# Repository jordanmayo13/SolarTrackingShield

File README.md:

# SolarTrackingSheild
ENGI 5800 Junior Design Project. An open source Arduino UNO R3 shield with room for a solar panel powered payload.

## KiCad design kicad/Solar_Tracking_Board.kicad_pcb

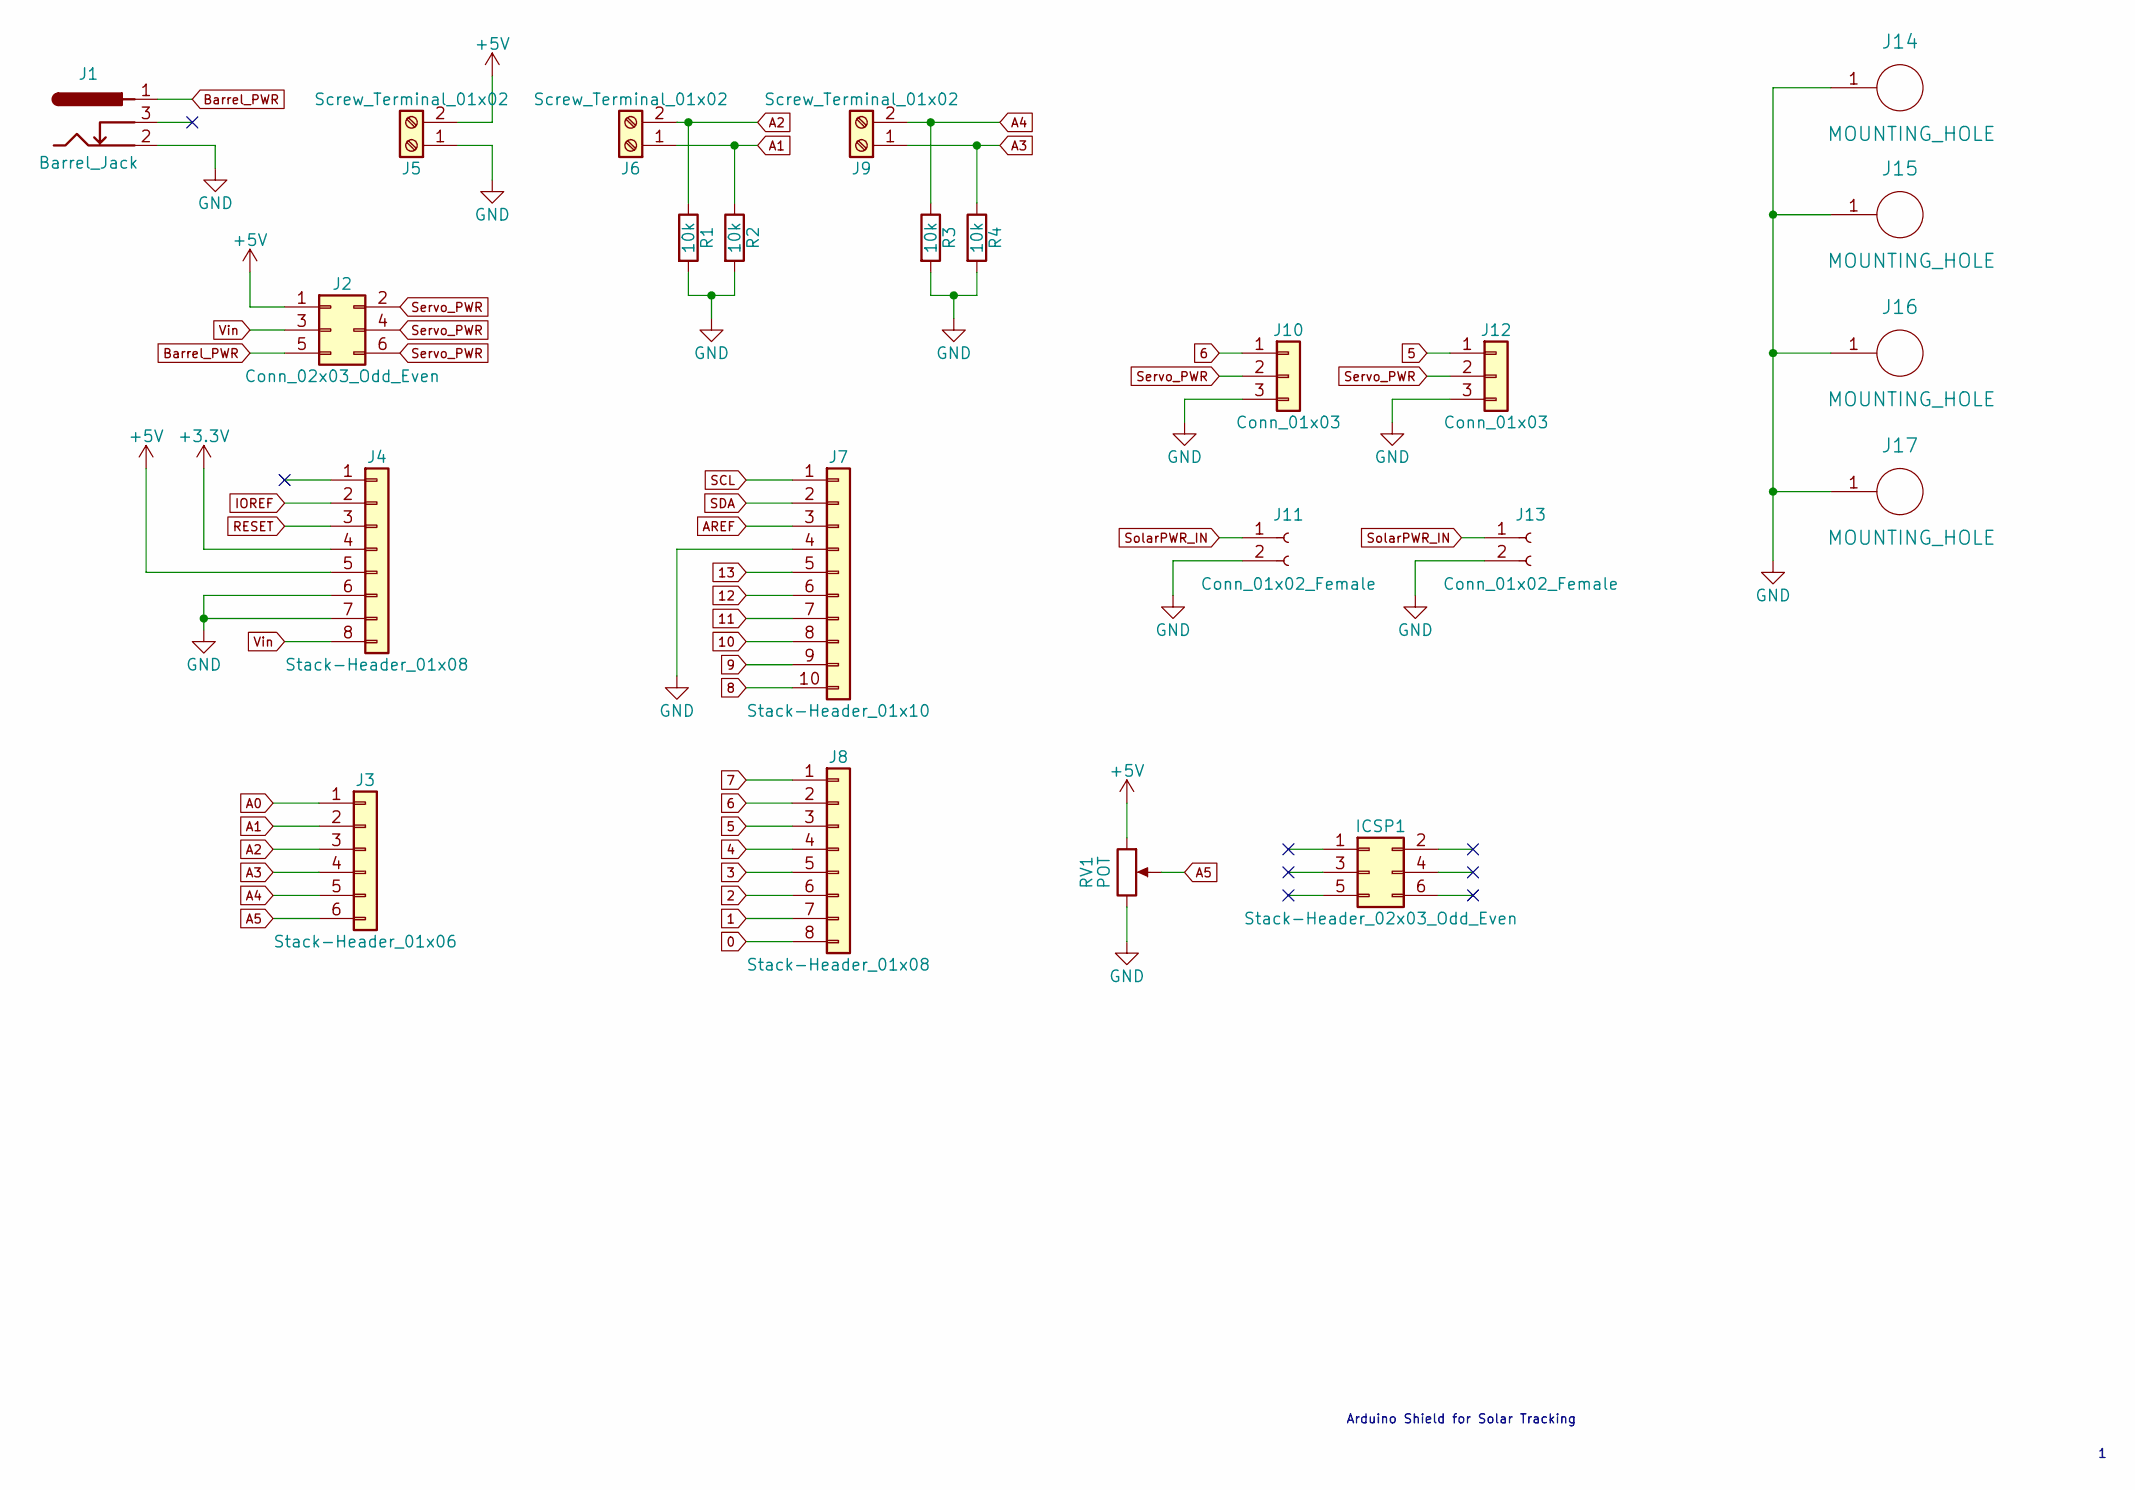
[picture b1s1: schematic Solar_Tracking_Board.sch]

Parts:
ICSP1: Stack-Header_02x03_Odd_Even; Pin_Header_Straight_2x03_Pitch2.54mm
J1: Barrel_Jack; Barrel_Jack_CUI_PJ-102AH
J2: Conn_02x03_Odd_Even; Pin_Header_Straight_2x03_Pitch2.54mm
J3: Stack-Header_01x06; Pin_Header_Straight_1x06_Pitch2.54mm
J4, J8: Stack-Header_01x08; Pin_Header_Straight_1x08_Pitch2.54mm
J5, J6, J9: Screw_Terminal_01x02; TerminalBlock_bornier-2_P5.08mm
J7: Stack-Header_01x10; Pin_Header_Straight_1x10_Pitch2.54mm
J10, J12: Conn_01x03; Pin_Header_Straight_1x03_Pitch2.54mm
J11, J13: Conn_01x02_Female; Pin_Header_Straight_1x02_Pitch2.54mm
J14, J15, J16, J17: MOUNTING_HOLE; MountingHole_3.2mm_M3_Pad
R1, R2, R3, R4: 10k; R_0805_HandSoldering
RV1: POT; Pin_Header_Straight_1x03_Pitch2.54mm

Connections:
0: J8.8
1: J8.7
2: J8.6
3: J8.5
4: J8.4
5: J8.3, J12.1
6: J8.2, J10.1
7: J8.1
8: J7.10
9: J7.9
10: J7.8
11: J7.7
12: J7.6
13: J7.5
+3V3: J4.4
+5V: J2.1, J4.5, J5.2, RV1.1
A0: J3.1
A1: J3.2, J6.1, R2.1
A2: J3.3, J6.2, R1.1
A3: J3.4, J9.1, R4.1
A4: J3.5, J9.2, R3.1
A5: J3.6, RV1.2
AREF: J7.3
Barrel_PWR: J1.1, J2.5
GND: J1.2, J4.6, J4.7, J5.1, J7.4, J10.3, J11.2, J12.3, J13.2, J14.1, J15.1, J16.1, J17.1, R1.2, R2.2, R3.2, R4.2, RV1.3
IOREF: J4.2
RESET: J4.3
SCL: J7.1
SDA: J7.2
Servo_PWR: J2.2, J2.4, J2.6, J10.2, J12.2
SolarPWR_IN: J11.1, J13.1
Vin: J2.3, J4.8

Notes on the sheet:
Arduino Shield for Solar Tracking

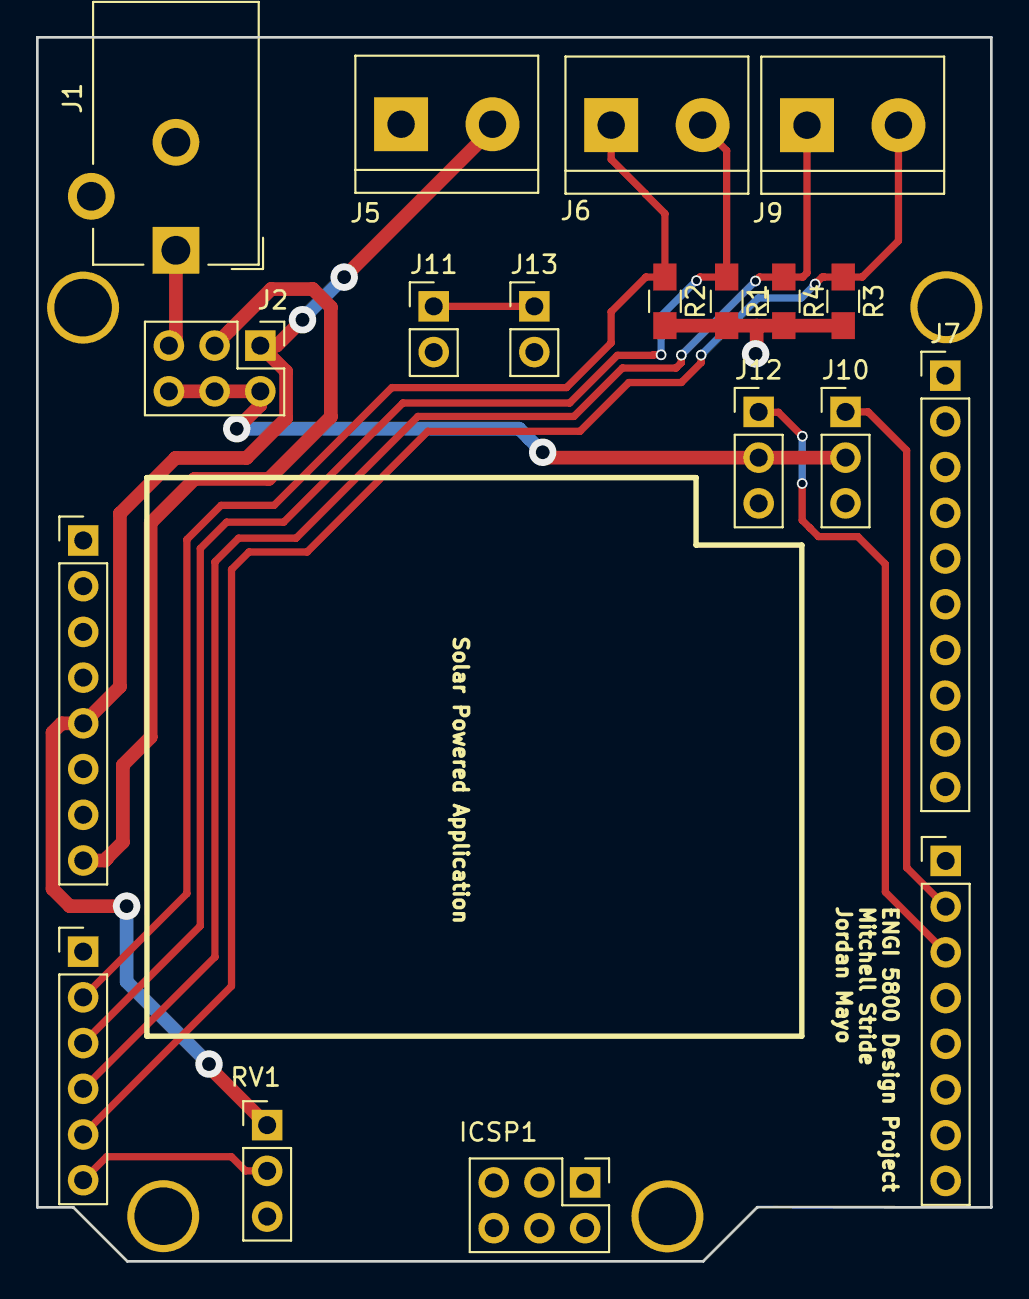
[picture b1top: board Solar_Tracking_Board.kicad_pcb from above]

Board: 2 copper layers, 53.0 x 68.0 mm, 23 parts (0 on the bottom side), 13 nets.

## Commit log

2018-01-09 Initial commit with schematic start
2018-01-09 spelling
2018-01-10 schematic footprints added
2018-01-10 schematic done
2018-01-10 layout started
2018-01-11 Board Rev1 finsihed
2018-01-11 Board Rev1 -ref fix
2018-01-25 Added folders for model and code
2018-01-29 Fake Render News
2018-01-29 added gerbers
2018-02-10 Updated Models
2018-02-10 creating pinout
2018-02-10 pinout added
2018-02-27 code update
2018-02-27 final render
2018-02-28 dicking around with avg
2018-03-07 added code v2
2018-03-07 added final models
2018-04-24 Create solartrackingfinal
    Final code used for demonstration pruposes
